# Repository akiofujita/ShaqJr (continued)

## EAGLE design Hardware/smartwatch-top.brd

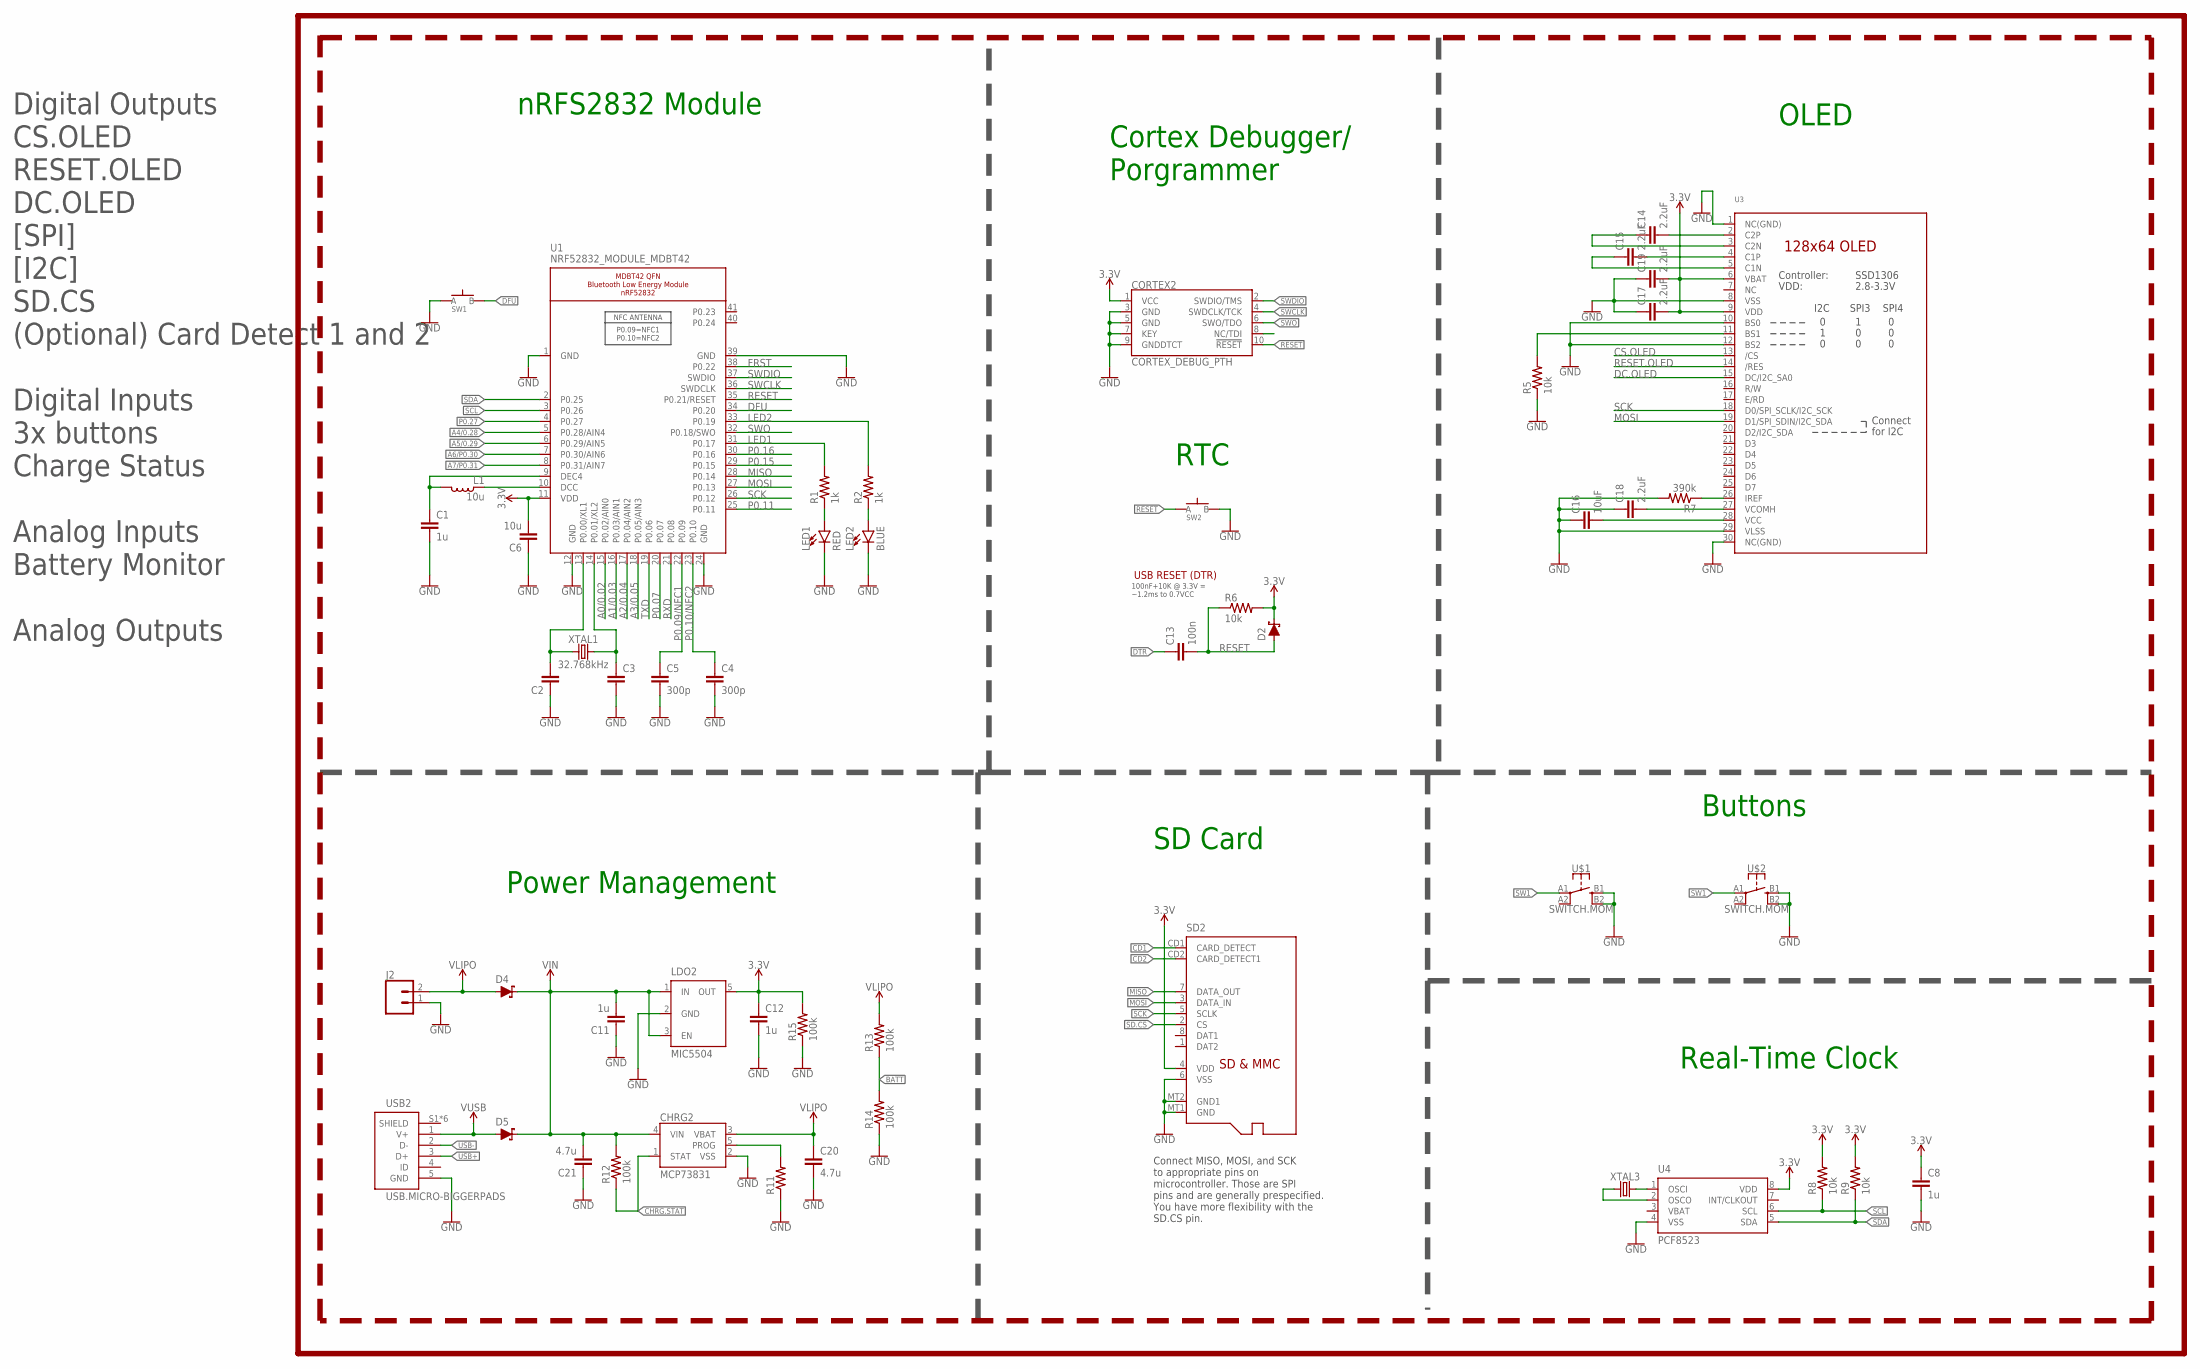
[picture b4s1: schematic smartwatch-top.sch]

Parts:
C1, C8, C11, C12: 1u; C0603
C2, C3: CAPACITOR0603; C0603
C4, C5: 300p; C0603
C6: 10u; C0805
C13: 100n; C0603
C14, C15, C17, C18, C19: 2.2uF; C0402
C16: 10uF; C0603
C20, C21: 4.7u; C0603
CHRG2: MCP73831; SOT23-5
CORTEX2: CORTEX_DEBUG_PTH; 2X5-PTH-1.27MM
D2, D4, D5: SCHOTTKY-USC; USC
J2: CONN_02; 1X02
L1: 10u; L0603
LDO2: MIC5504; SOT23-5
LED1: RED; LED-0603
LED2: BLUE; LED-0603
R1, R2: 1k; R0603
R5, R6, R8, R9: 10k; R0603
R7: 390k; R0603
R11: RESISTOR0603; R0603
R12, R13, R14, R15: 100k; R0603
SD2: MICROSD
SW1, SW2: SPST-PTS830GG140-COPY.1-3; BUTTON-GULLWING
U1: NRF52832_MODULE_MDBT42; BLE_MODULE_RAYTAC_MDBT42
U3: DISP_OLED_UG-2864HSWEG01-NO-WRAPAROUND; UG-2864HSWEG01_0.96IN_NO-WRAPAROUND
U4: PCF8523; SO8
U$1, U$2: SWITCH.MOM; TACTILE_SWITCH_SMD_6.2MM_TALL
USB2: USB.MICRO-BIGGERPADS; USB-MICRO-01.BIGGERPADS
XTAL1: 32.768kHz; 2-SMD.NOLEAD.2.0MMTO1.2MM
XTAL3: CRYSTALECS-.327-12.5-12-C-TR; 2-SMD.NOLEAD.2.0MMTO1.2MM

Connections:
3.3V: C6.2, C8.1, C12.1, C17.2, C19.2, CORTEX2.1 (VCC), D2.- (C), LDO2.5 (OUT), R6.2, R8.2, R9.2, R15.2, SD2.4 (VDD), U1.11 (VDD), U3.6 (VBAT), U3.9 (VDD), U4.8 (VDD)
A0/0.02: U1.15 (P0.02/AIN0)
A1/0.03: U1.16 (P0.03/AIN1)
A2/0.04: U1.17 (P0.04/AIN2)
A3/0.05: U1.18 (P0.05/AIN3)
A4/0.28: U1.5 (P0.28/AIN4)
A5/0.29: U1.6 (P0.29/AIN5)
A6/P0.30: U1.7 (P0.30/AIN6)
A7/P0.31: U1.8 (P0.31/AIN7)
BATT: R13.1, R14.2
CD1: SD2.CD1 (CARD_DETECT)
CD2: SD2.CD2 (CARD_DETECT1)
CHRG.STAT: CHRG2.1 (STAT), R12.1
CS.OLED: U3.13 (/CS)
DC.OLED: U3.15 (DC/I2C_SA0)
DFU: SW1.3 (B), U1.34 (P0.20)
DTR: C13.1
FRST: U1.38 (P0.22)
GND: C1.2, C2.1, C3.2, C4.2, C5.2, C6.1, C8.2, C11.1, C12.2, C16.1, C17.1, C18.1, C19.1, C20.2, C21.1, CHRG2.2 (VSS), CORTEX2.3 (GND), CORTEX2.5 (GND), CORTEX2.7 (KEY), CORTEX2.9 (GNDDTCT), J2.1, LDO2.2 (GND), LED1.C, LED2.C, R5.1, R7.2, R11.1, R14.1, R15.1, SD2.6 (VSS), SD2.MT1 (GND), SD2.MT2 (GND1), SW1.1 (A), SW2.3 (B), U1.1 (GND), U1.12 (GND), U1.24 (GND), U1.39 (GND), U3.1 (NC(GND)), U3.8 (VSS), U3.10 (BS0), U3.12 (BS2), U3.29 (VLSS), U3.30 (NC(GND)), U4.4 (VSS), USB2.5 (GND)
LED1: R1.2, U1.31 (P0.17)
LED2: R2.2, U1.33 (P0.19)
MISO: SD2.7 (DATA_OUT), U1.28 (P0.14)
MOSI: SD2.3 (DATA_IN), U1.27 (P0.13), U3.19 (D1/SPI_SDIN/I2C_SDA)
unnamed: C2.2, U1.13 (P0.00/XL1), XTAL1.P$1 (1)
unnamed: C3.1, U1.14 (P0.01/XL2), XTAL1.P$2 (2)
unnamed: L1.1, U1.10 (DCC)
unnamed: R5.2, U3.11 (BS1)
unnamed: LED1.A, R1.1
unnamed: R7.1, U3.26 (IREF)
unnamed: LED2.A, R2.1
unnamed: C1.1, L1.2, U1.9 (DEC4)
unnamed: C14.2, U3.2 (C2P)
unnamed: C14.1, U3.3 (C2N)
unnamed: C15.2, U3.4 (C1P)
unnamed: C15.1, U3.5 (C1N)
unnamed: C16.2, U3.28 (VCC)
unnamed: C18.2, U3.27 (VCOMH)
unnamed: U$1.B1 (3), U$1.B2 (4), U$2.B1 (3), U$2.B2 (4)
unnamed: CHRG2.5 (PROG), R11.2
unnamed: U4.2 (OSCO), XTAL3.P$1 (1)
unnamed: U4.1 (OSCI), XTAL3.P$2 (2)
P0.07: U1.20 (P0.07)
P0.09/NFC1: C5.1, U1.22 (P0.09)
P0.10/NFC2: C4.1, U1.23 (P0.10)
P0.11: U1.25 (P0.11)
P0.15: U1.29 (P0.15)
P0.16: U1.30 (P0.16)
P0.27: U1.4 (P0.27)
RESET: C13.2, CORTEX2.10 (!RESET), D2.+ (A), R6.1, SW2.1 (A), U1.35 (P0.21/RESET)
RESET.OLED: U3.14 (/RES)
RXD: U1.21 (P0.08)
SCK: SD2.5 (SCLK), U1.26 (P0.12), U3.18 (D0/SPI_SCLK/I2C_SCK)
SCL: R8.1, U1.3 (P0.26), U4.6 (SCL)
SD.CS: SD2.2 (CS)
SDA: R9.1, U1.2 (P0.25), U4.5 (SDA)
SW1: U$1.A1 (1), U$2.A1 (1)
SWCLK: CORTEX2.4 (SWDCLK/TCK), U1.36 (SWDCLK)
SWDIO: CORTEX2.2 (SWDIO/TMS), U1.37 (SWDIO)
SWO: CORTEX2.6 (SWO/TDO), U1.32 (P0.18/SWO)
TXD: U1.19 (P0.06)
USB+: USB2.3 (D+)
USB-: USB2.2 (D-)
VBAT: U4.3 (VBAT)
VIN: C11.2, C21.2, CHRG2.4 (VIN), D4.- (C), D5.- (C), LDO2.1 (IN), LDO2.3 (EN), R12.2
VLIPO: C20.1, CHRG2.3 (VBAT), D4.+ (A), J2.2, R13.2
V_USB: D5.+ (A), USB2.1 (V+)

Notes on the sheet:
USB RESET (DTR)
100nF+10K @ 3.3V = ~1.2ms to 0.7VCC
Connect MISO, MOSI, and SCK to appropriate pins on microcontroller. Those are SPI pins and are generally prespecified. You have more flexibility with the SD.CS pin.
nRFS2832 Module
OLED
Power Management
SD Card
Buttons
Real-Time Clock
Cortex Debugger/ Porgrammer
RTC
Digital Outputs CS.OLED RESET.OLED DC.OLED [SPI] [I2C] SD.CS (Optional) Card Detect 1 and 2 Digital Inputs 3x buttons Charge Status Analog Inputs Battery Monitor Analog Outputs

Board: 2 copper layers, 51 parts (2 on the bottom side), 40 nets, no tracks yet.

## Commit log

2020-02-02 Adding hardware and firmware folders- arduino and sch and brd files
2020-04-18 added smartwatch-top and smartwatch-bottom files for EAGLE
2020-05-28 features list
2020-06-04 Added top, bottom, pcb module folders
2020-06-04 added ppg-module folder
2020-06-04 deleted random text file
2020-06-04 adding ppg-module once again
2020-06-04 added BOM files
2020-06-04 deleted unnecessary files
2020-06-18 Finished Take003
2020-06-18 Rename smartwatch-top.sch to ShaqJr-TOP.sch
    Renamed file to align with instructions
2020-06-18 Rename smartwatch-top.brd to ShaqJr-TOP.brd
    Renamed file to align with instructions
2020-06-18 Rename smartwatch-bottom.brd to ShaqJr-BOTTOM.brd
    Renamed file to align with instructions
2020-06-18 Rename smartwatch-bottom.sch to ShaqJr-BOTTOM.sch
    Renamed file to align with instructions
2020-06-25 completed 2020 05 02 tutorial for OOP
2020-07-10 completed take 007, may need to review polygons- gnd and 3.3v
2020-07-17 Finished Take 008
2020-08-13 Added ppg module brd, sch and bom, and ex ino code
2020-08-14 Added basic list for BOM
2020-08-14 Organized BOM parts in a more reasonable order and added quantities
